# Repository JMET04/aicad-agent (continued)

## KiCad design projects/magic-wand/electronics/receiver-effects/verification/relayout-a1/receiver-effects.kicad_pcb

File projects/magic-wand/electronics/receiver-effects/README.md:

# Receiver Effects A0

Status: design input only; fabrication is blocked.

This is the independent media receiver direction. It is intentionally separate
from both the existing receiver baseline and the wand order. It contains only
the NINA-B302 radio/MCU concept, protected 5 V / 2 A USB-C input, 3.3 V logic,
an 8-pin GC9A01A module interface, MAX98357A I2S amplifier with differential
4 ohm speaker connector, and a discrete 3.3 V RGB status LED. Legacy UART,
optocoupler and 12 V MOSFET actuator channels are not copied.

The exact pin, power, effect and resource design inputs are in
receiver-effects-contract.json. fabrication-gate.json is authoritative for
ordering: there are no KiCad sources, native ERC/DRC, Gerber, drill, qualified
BOM or placement files yet, so fabrication_authorized is false.

The portable firmware can host-test eight isolated sessions and procedural
display/audio effects. That evidence does not close target, power, RF, EMC,
thermal, acoustic or manufacturing gates.

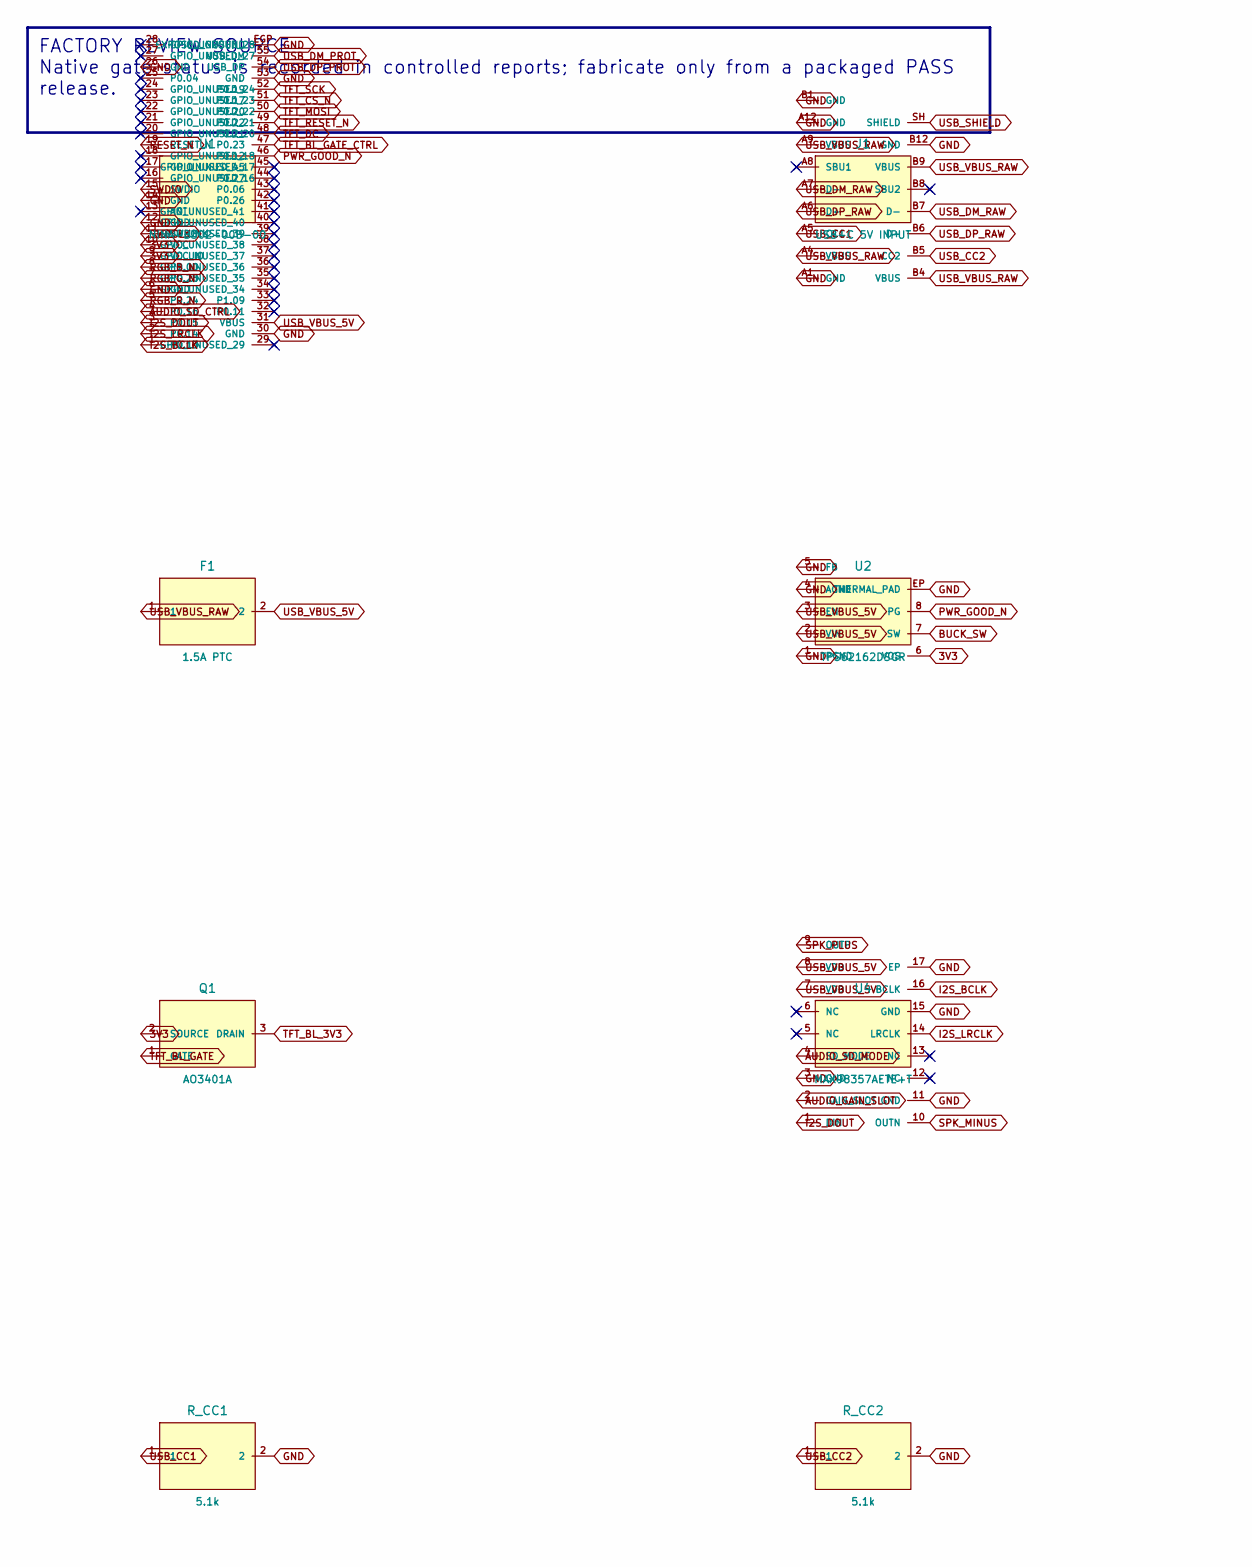
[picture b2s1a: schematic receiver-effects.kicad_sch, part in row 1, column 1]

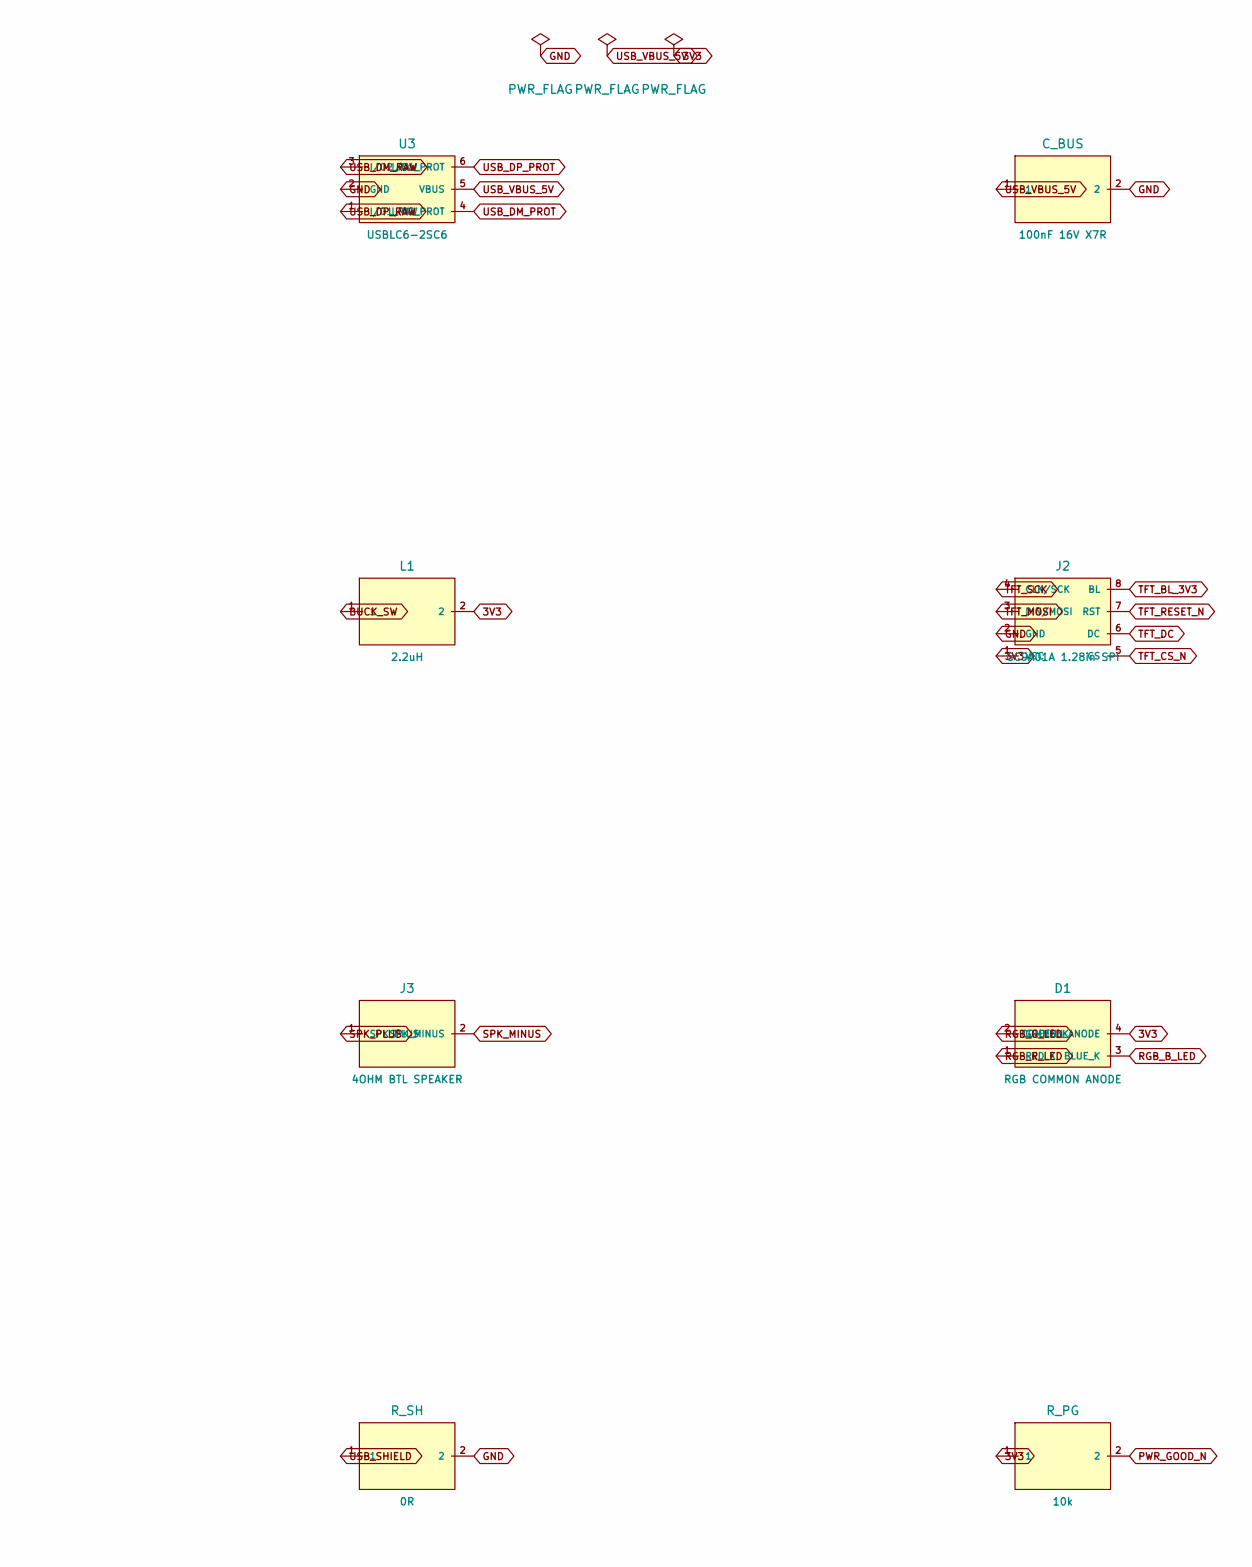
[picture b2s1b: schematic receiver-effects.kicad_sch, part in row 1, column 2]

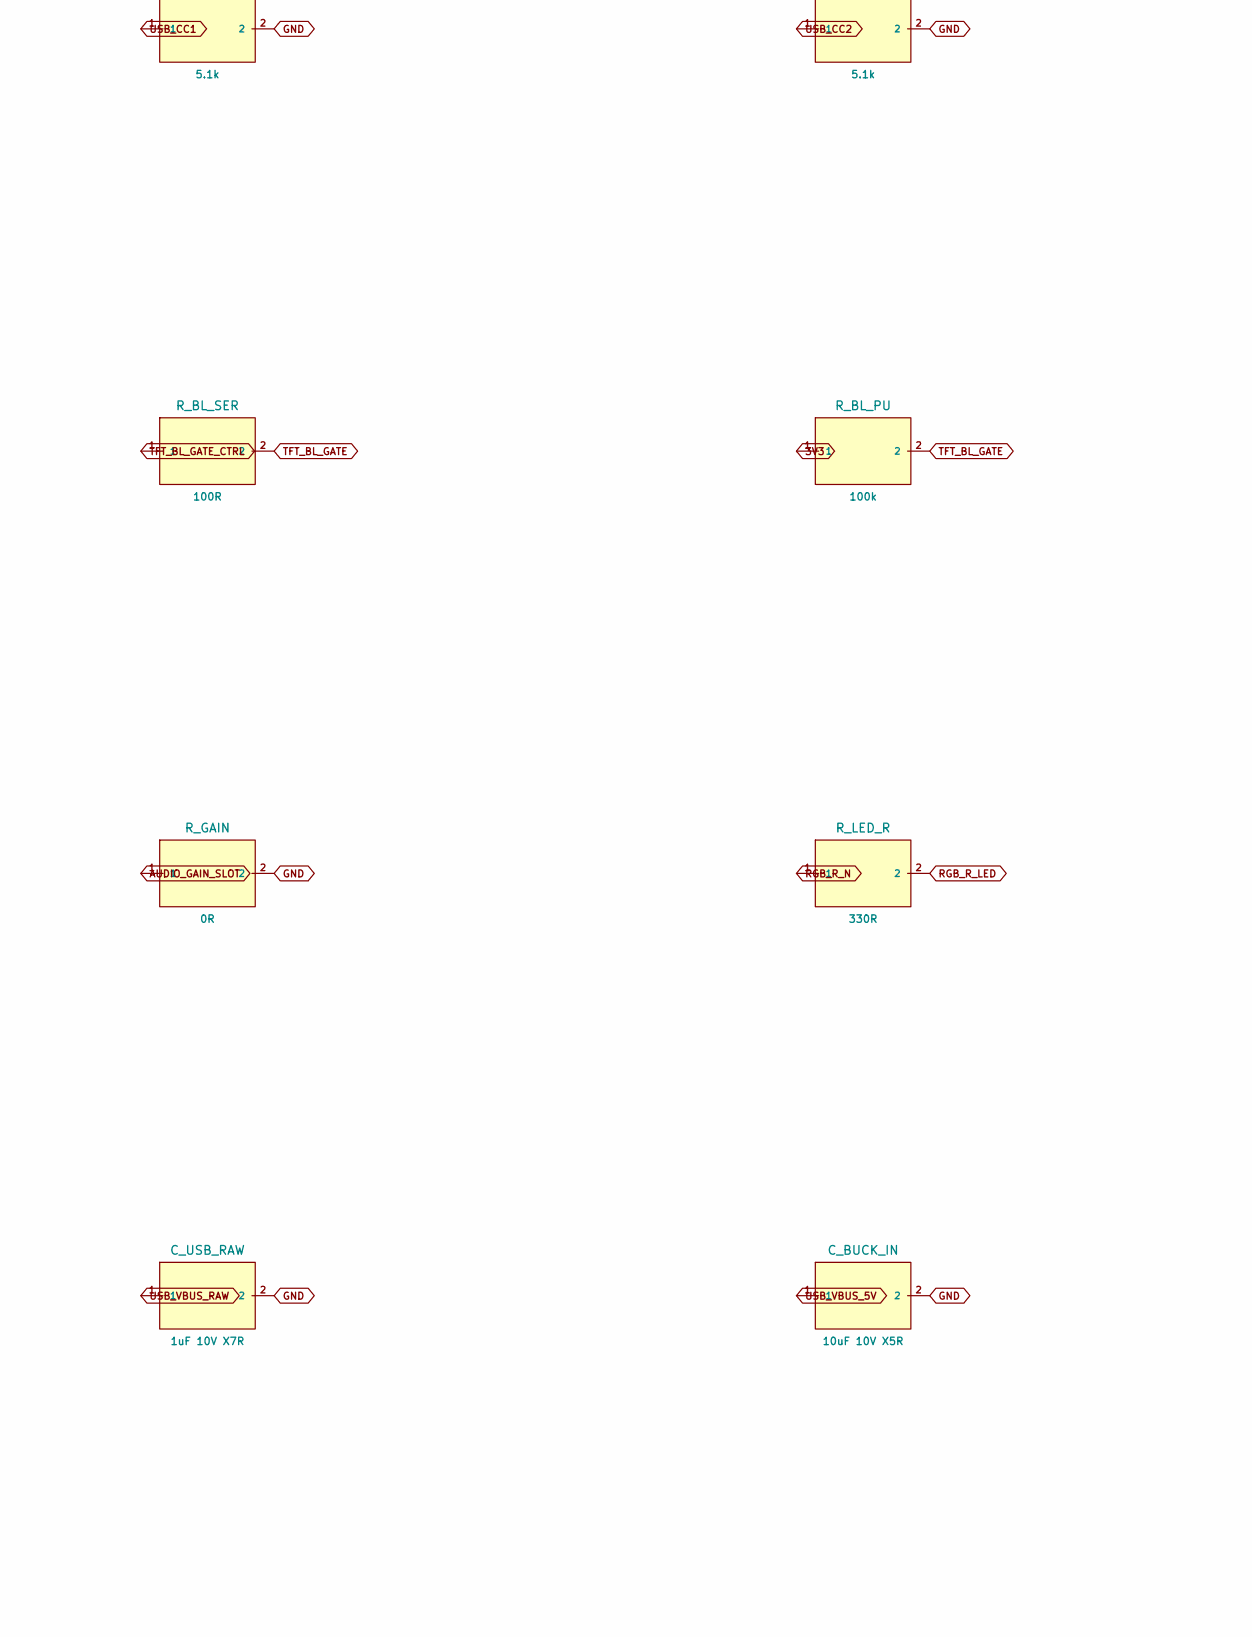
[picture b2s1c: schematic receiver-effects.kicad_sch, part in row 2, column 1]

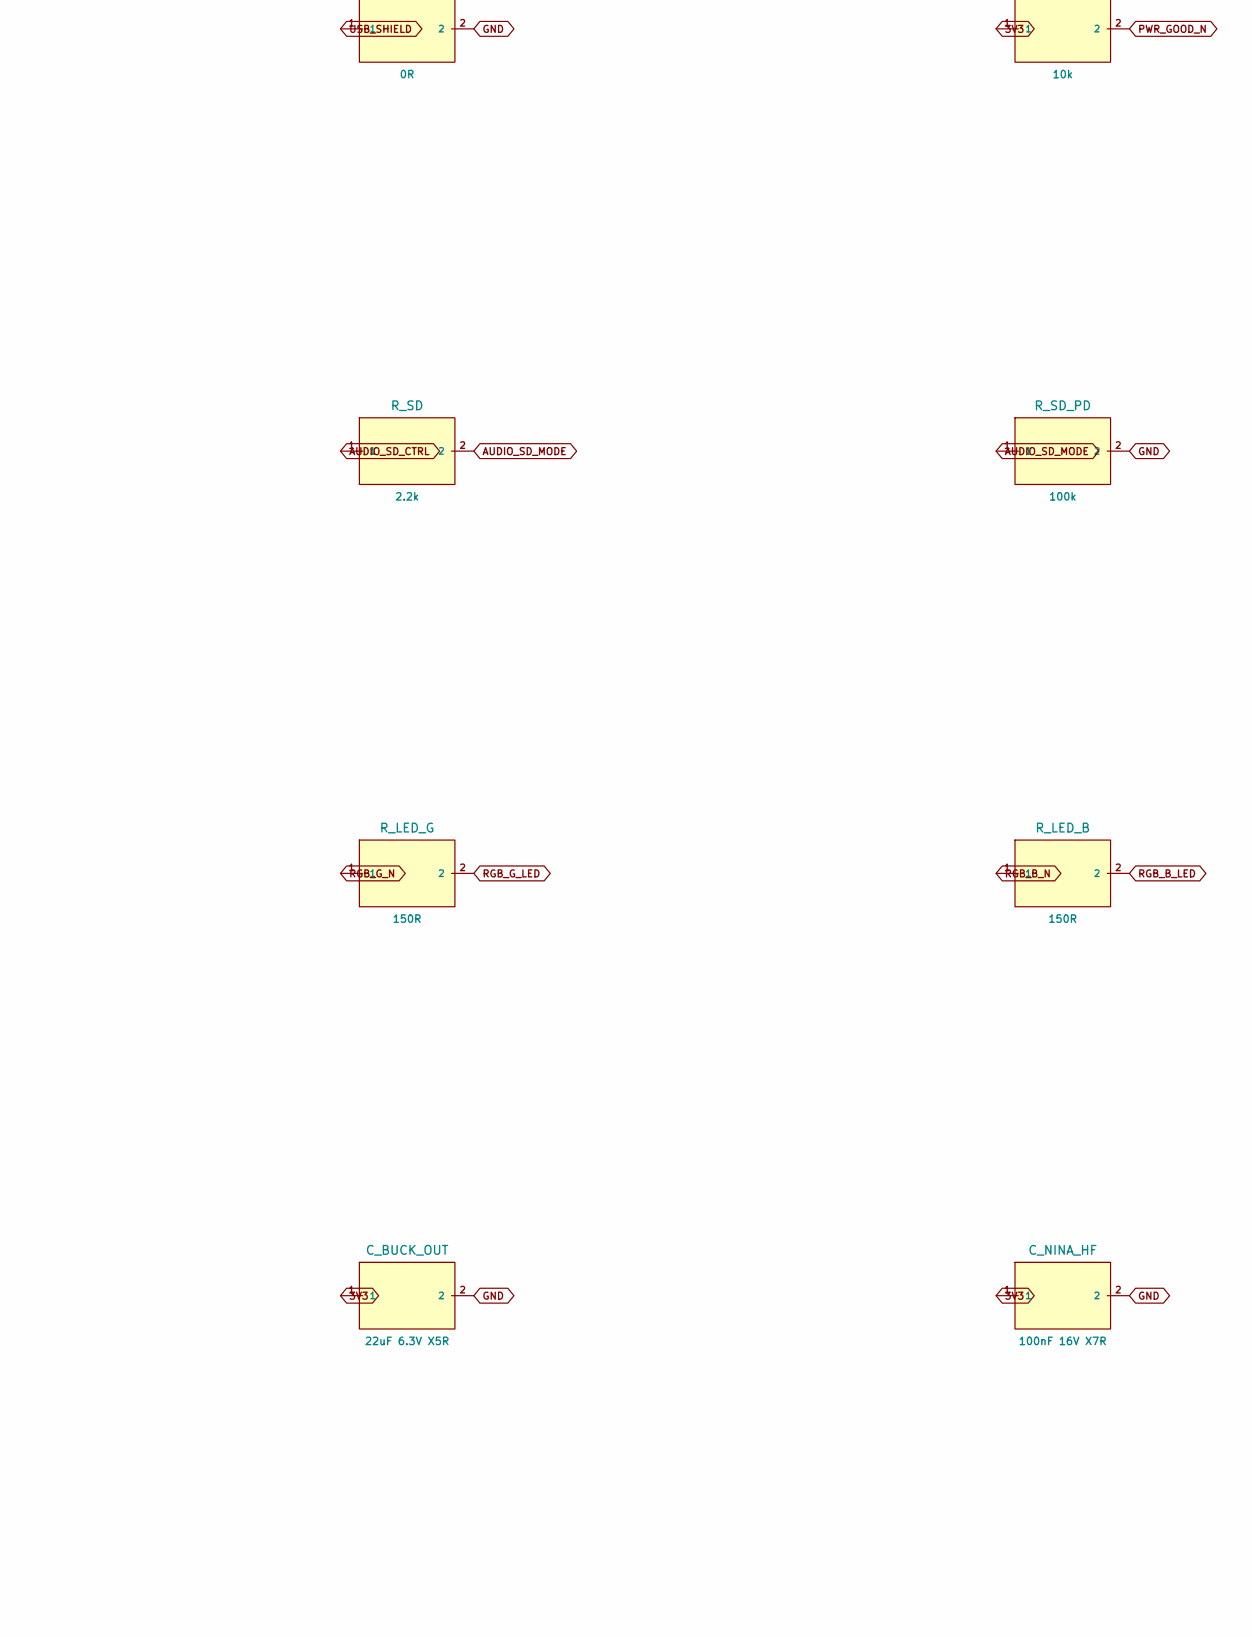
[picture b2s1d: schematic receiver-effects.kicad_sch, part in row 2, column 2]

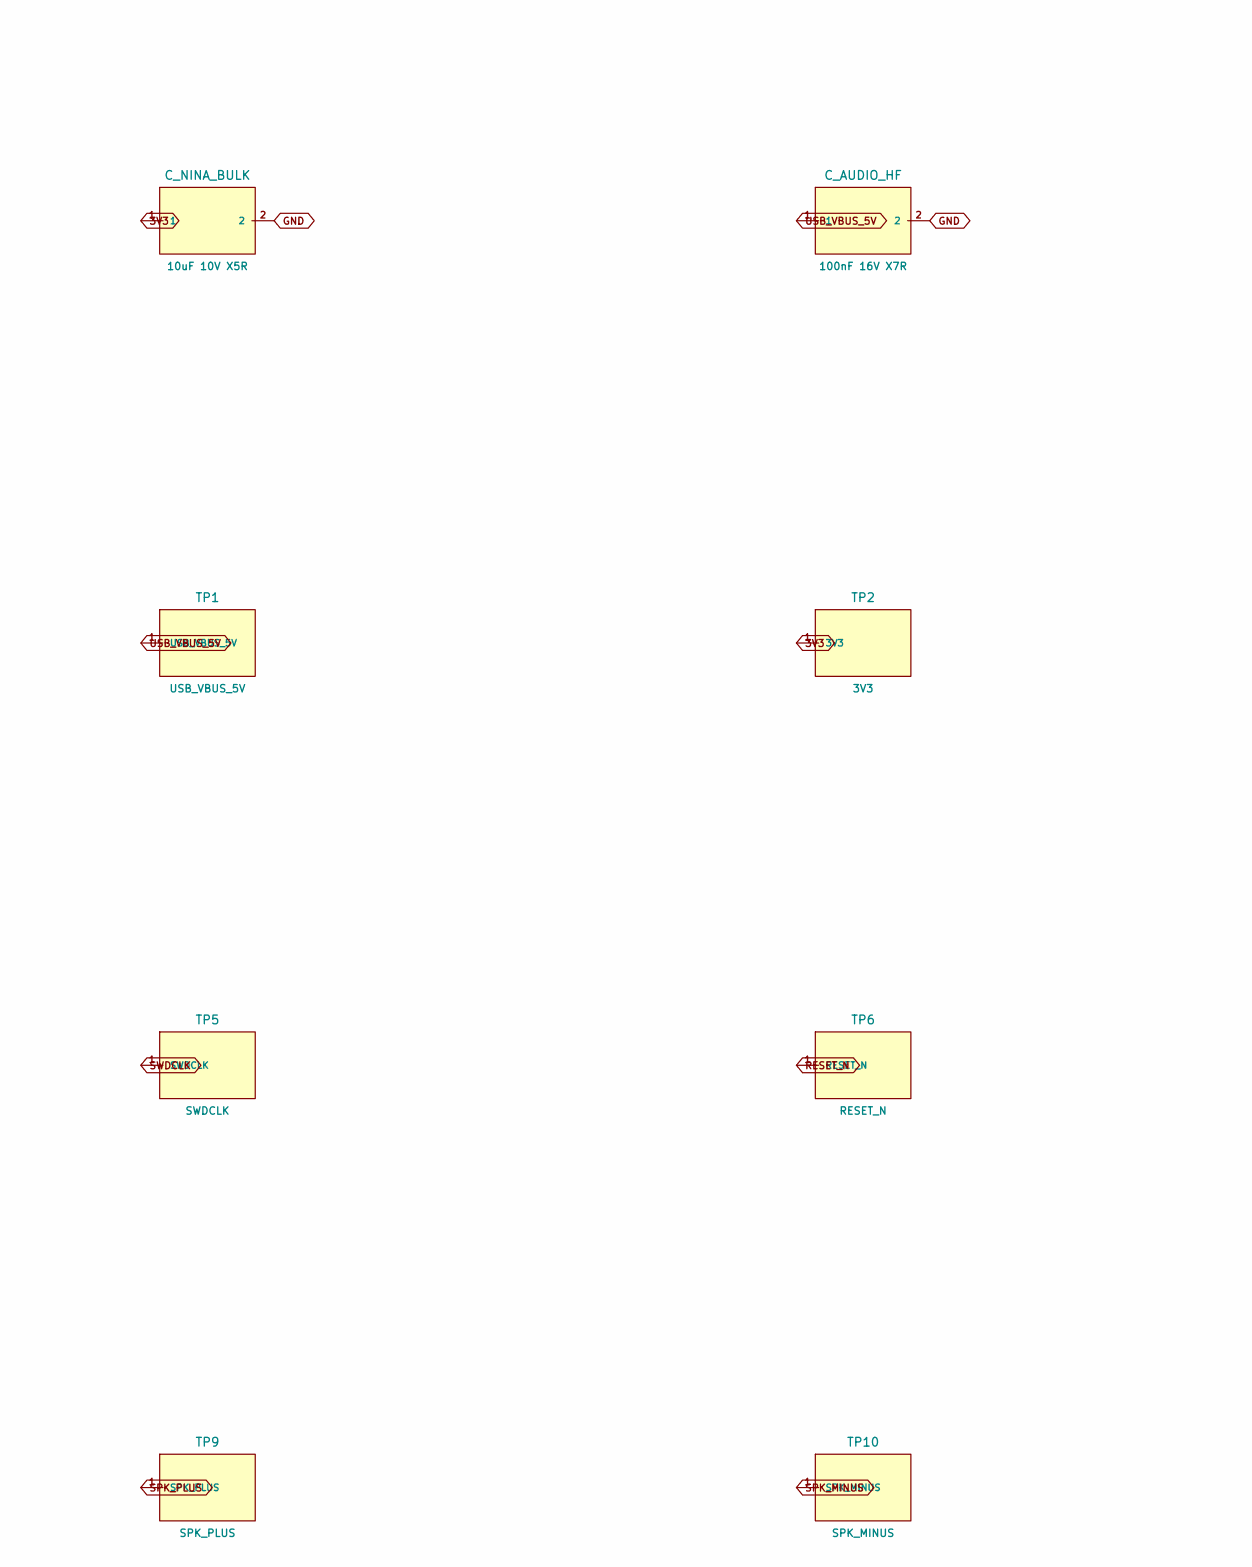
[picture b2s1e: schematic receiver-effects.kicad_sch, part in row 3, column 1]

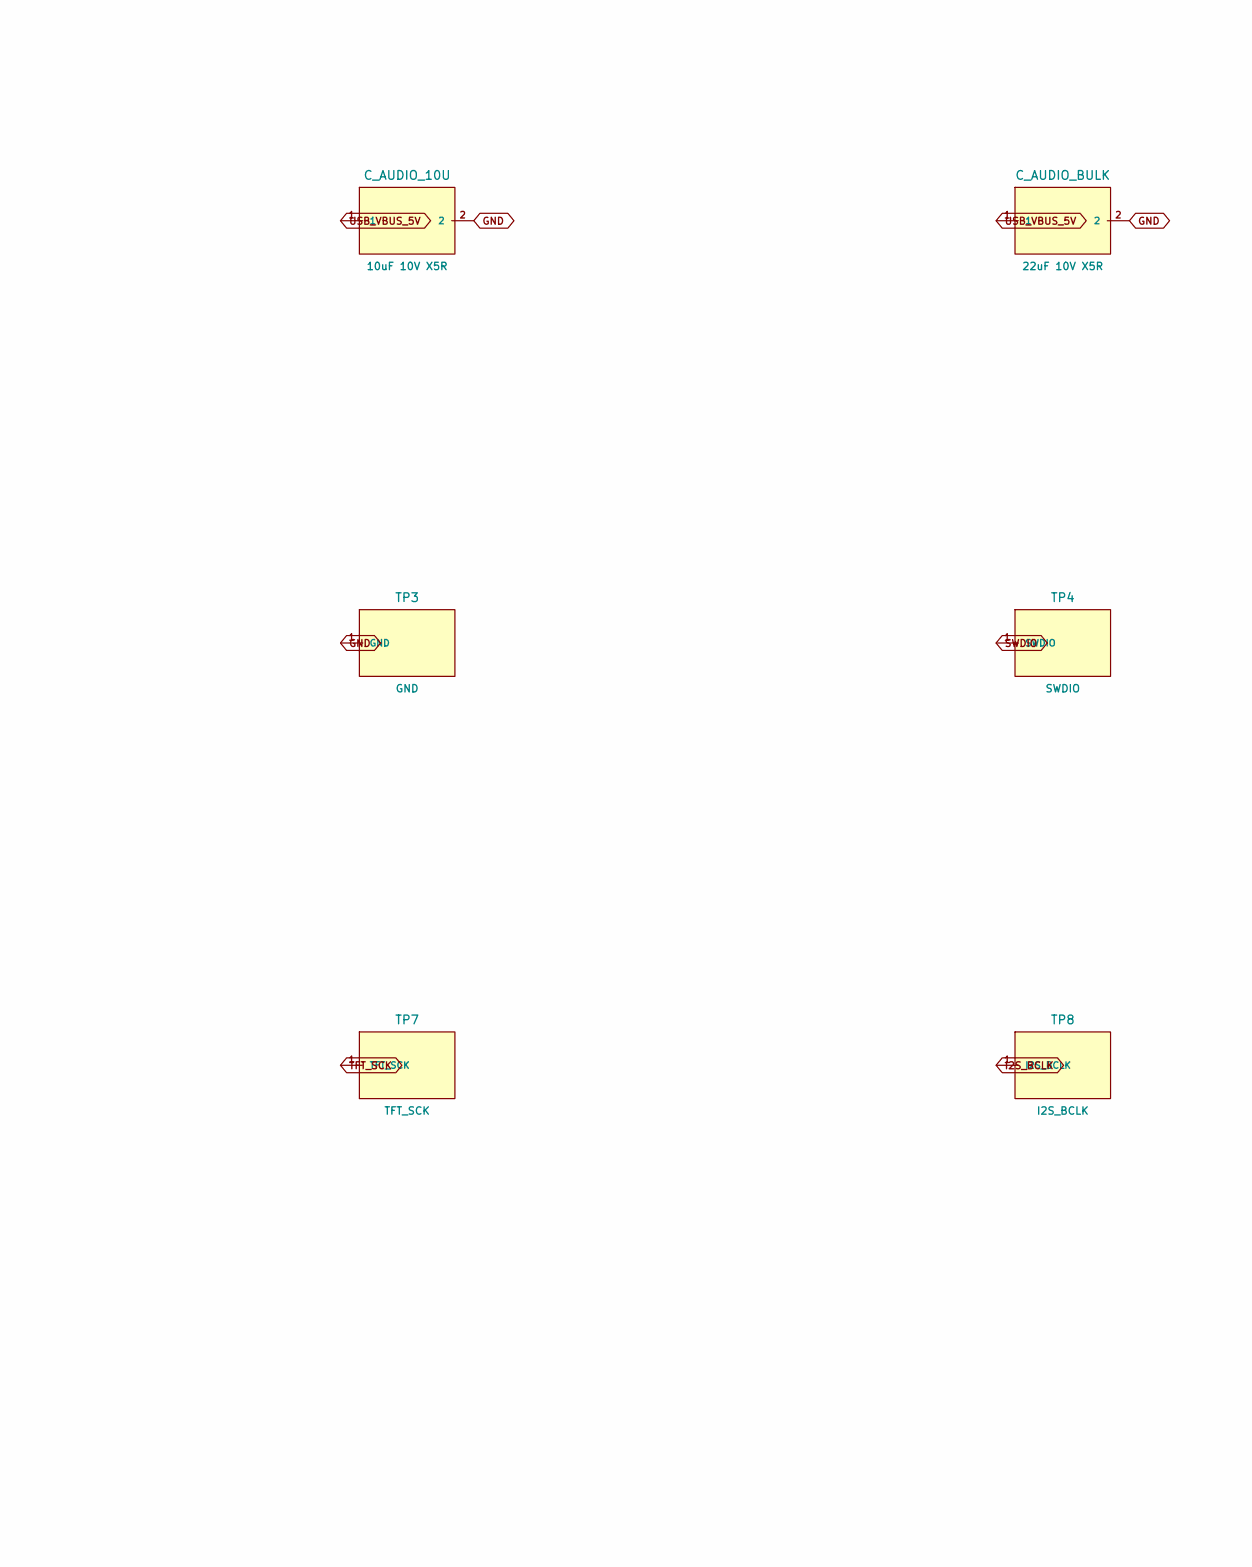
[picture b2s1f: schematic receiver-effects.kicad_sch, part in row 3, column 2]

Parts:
C_AUDIO_10U: 10uF 10V X5R; receiver-effects_C_AUDIO_10U; MPN GRM21BR61A106KE19L; LCSC C77073
C_AUDIO_BULK: 22uF 10V X5R; receiver-effects_C_AUDIO_BULK; MPN GRM21BR61A226ME44L; LCSC C441864
C_AUDIO_HF: 100nF 16V X7R; receiver-effects_C_AUDIO_HF; MPN GRM155R71C104KA88D; LCSC C1525
C_BUCK_IN: 10uF 10V X5R; receiver-effects_C_BUCK_IN; MPN GRM21BR61A106KE19L; LCSC C77073
C_BUCK_OUT: 22uF 6.3V X5R; receiver-effects_C_BUCK_OUT; MPN GRM21BR60J226ME39L; LCSC C77071
C_BUS: 100nF 16V X7R; receiver-effects_C_BUS; MPN GRM155R71C104KA88D; LCSC C1525
C_NINA_BULK: 10uF 10V X5R; receiver-effects_C_NINA_BULK; MPN GRM21BR61A106KE19L; LCSC C77073
C_NINA_HF: 100nF 16V X7R; receiver-effects_C_NINA_HF; MPN GRM155R71C104KA88D; LCSC C1525
C_USB_RAW: 1uF 10V X7R; receiver-effects_C_USB_RAW; MPN GRM155R71A105KE15D
D1: RGB COMMON ANODE; receiver-effects_D1; MPN LTST-C19HE1WT; LCSC C458749
F1: 1.5A PTC; receiver-effects_F1; MPN MF-MSMF150/24X-2; LCSC C78695
J1: USB-C 5V INPUT; receiver-effects_J1; MPN USB4105-GF-A-120; LCSC C5184243
J2: GC9A01A 1.28in SPI; receiver-effects_J2; MPN SM08B-GHS-TB(LF)(SN); LCSC C265111
J3: 4OHM BTL SPEAKER; receiver-effects_J3; MPN S2B-PH-SM4-TB(LF)(SN); LCSC C295747
L1: 2.2uH; receiver-effects_L1; MPN LQH32PN2R2NN0L
Q1: AO3401A; receiver-effects_Q1; MPN AO3401A; LCSC C15127
R_BL_PU: 100k; receiver-effects_R_BL_PU; MPN RC0402FR-07100KL; LCSC C25741
R_BL_SER: 100R; receiver-effects_R_BL_SER; MPN RC0402FR-07100RL; LCSC C25076
R_CC1: 5.1k; receiver-effects_R_CC1; MPN RC0402FR-075K1L; LCSC C25905
R_CC2: 5.1k; receiver-effects_R_CC2; MPN RC0402FR-075K1L; LCSC C25905
R_GAIN: 0R; receiver-effects_R_GAIN; MPN RC0402JR-070RL; LCSC C17168
R_LED_B: 150R; receiver-effects_R_LED_B; MPN RC0402FR-07150RL; LCSC C25082
R_LED_G: 150R; receiver-effects_R_LED_G; MPN RC0402FR-07150RL; LCSC C25082
R_LED_R: 330R; receiver-effects_R_LED_R; MPN RC0402FR-07330RL; LCSC C25104
R_PG: 10k; receiver-effects_R_PG; MPN RC0402FR-0710KL; LCSC C25744
R_SD: 2.2k; receiver-effects_R_SD; MPN RC0402FR-072K2L; LCSC C25879
R_SD_PD: 100k; receiver-effects_R_SD_PD; MPN RC0402FR-07100KL; LCSC C25741
R_SH: 0R; receiver-effects_R_SH; MPN RC0402JR-070RL; LCSC C17168
TP1: USB_VBUS_5V; receiver-effects_TP1; MPN BARE_PAD_D1.5
TP2: 3V3; receiver-effects_TP2; MPN BARE_PAD_D1.5
TP3: GND; receiver-effects_TP3; MPN BARE_PAD_D1.5
TP4: SWDIO; receiver-effects_TP4; MPN BARE_PAD_D1.5
TP5: SWDCLK; receiver-effects_TP5; MPN BARE_PAD_D1.5
TP6: RESET_N; receiver-effects_TP6; MPN BARE_PAD_D1.5
TP7: TFT_SCK; receiver-effects_TP7; MPN BARE_PAD_D1.5
TP8: I2S_BCLK; receiver-effects_TP8; MPN BARE_PAD_D1.5
TP9: SPK_PLUS; receiver-effects_TP9; MPN BARE_PAD_D1.5
TP10: SPK_MINUS; receiver-effects_TP10; MPN BARE_PAD_D1.5
U1: NINA-B302-00B-00; receiver-effects_U1; MPN NINA-B302-00B-00; LCSC C6335962
U2: TPS62162DSGR; receiver-effects_U2; MPN TPS62162DSGR; LCSC C40256
U3: USBLC6-2SC6; receiver-effects_U3; MPN USBLC6-2SC6; LCSC C7519
U4: MAX98357AETE+T; receiver-effects_U4; MPN MAX98357AETE+T; LCSC C910544

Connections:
3V3: C_BUCK_OUT.1, C_NINA_BULK.1, C_NINA_HF.1, D1.4 (COMMON_ANODE), J2.1 (VCC), L1.2, Q1.2 (SOURCE), R_BL_PU.1, R_PG.1, TP2.1 (3V3), U1.9 (VCC_IO), U1.10 (VCC), U2.6 (VOS)
AUDIO_GAIN_SLOT: R_GAIN.1, U4.2 (GAIN_SLOT)
AUDIO_SD_CTRL: R_SD.1, U1.4 (P0.16)
AUDIO_SD_MODE: R_SD.2, R_SD_PD.1, U4.4 (SD_MODE)
BUCK_SW: L1.1, U2.7 (SW)
GND: C_AUDIO_10U.2, C_AUDIO_BULK.2, C_AUDIO_HF.2, C_BUCK_IN.2, C_BUCK_OUT.2, C_BUS.2, C_NINA_BULK.2, C_NINA_HF.2, C_USB_RAW.2, J1.A1 (GND), J1.A12 (GND), J1.B1 (GND), J1.B12 (GND), J2.2 (GND), R_CC1.2, R_CC2.2, R_GAIN.2, R_SD_PD.2, R_SH.2, TP3.1 (GND), U1.6 (GND), U1.12 (GND), U1.14 (GND), U1.26 (GND), U1.30 (GND), U1.53 (GND), U1.EGP (EXPOSED_GROUND), U2.1 (PGND), U2.4 (AGND), U2.5 (FB), U2.EP (THERMAL_PAD), U3.2 (GND), U4.3 (GND), U4.11 (GND), U4.15 (GND), U4.17 (EP)
I2S_BCLK: TP8.1 (I2S_BCLK), U1.1 (P0.13), U4.16 (BCLK)
I2S_DOUT: U1.3 (P0.15), U4.1 (DIN)
I2S_LRCLK: U1.2 (P0.14), U4.14 (LRCLK)
PWR_GOOD_N: R_PG.2, U1.46 (P0.12), U2.8 (PG)
RESET_N: TP6.1 (RESET_N), U1.19 (RESET_N)
RGB_B_LED: D1.3 (BLUE_K), R_LED_B.2
RGB_B_N: R_LED_B.1, U1.8 (P1.00)
RGB_G_LED: D1.2 (GREEN_K), R_LED_G.2
RGB_G_N: R_LED_G.1, U1.7 (P0.25)
RGB_R_LED: D1.1 (RED_K), R_LED_R.2
RGB_R_N: R_LED_R.1, U1.5 (P0.24)
SPK_MINUS: J3.2 (SPK_MINUS), TP10.1 (SPK_MINUS), U4.10 (OUTN)
SPK_PLUS: J3.1 (SPK_PLUS), TP9.1 (SPK_PLUS), U4.9 (OUTP)
SWDCLK: TP5.1 (SWDCLK), U1.11 (SWDCLK)
SWDIO: TP4.1 (SWDIO), U1.15 (SWDIO)
TFT_BL_3V3: J2.8 (BL), Q1.3 (DRAIN)
TFT_BL_GATE: Q1.1 (GATE), R_BL_PU.2, R_BL_SER.2
TFT_BL_GATE_CTRL: R_BL_SER.1, U1.47 (P0.23)
TFT_CS_N: J2.5 (CS), U1.51 (P0.17)
TFT_DC: J2.6 (DC), U1.48 (P0.21)
TFT_MOSI: J2.3 (DIN/MOSI), U1.50 (P0.20)
TFT_RESET_N: J2.7 (RST), U1.49 (P0.22)
TFT_SCK: J2.4 (CLK/SCK), TP7.1 (TFT_SCK), U1.52 (P0.19)
USB_CC1: J1.A5 (CC1), R_CC1.1
USB_CC2: J1.B5 (CC2), R_CC2.1
USB_DM_PROT: U1.55 (USB_DM), U3.4 (I/O2_PROT)
USB_DM_RAW: J1.A7 (D-), J1.B7 (D-), U3.3 (I/O2_RAW)
USB_DP_PROT: U1.54 (USB_DP), U3.6 (I/O1_PROT)
USB_DP_RAW: J1.A6 (D+), J1.B6 (D+), U3.1 (I/O1_RAW)
USB_SHIELD: J1.SH (SHIELD), R_SH.1
USB_VBUS_5V: C_AUDIO_10U.1, C_AUDIO_BULK.1, C_AUDIO_HF.1, C_BUCK_IN.1, C_BUS.1, F1.2, TP1.1 (USB_VBUS_5V), U1.31 (VBUS), U2.2 (VIN), U2.3 (EN), U3.5 (VBUS), U4.7 (VDD), U4.8 (VDD)
USB_VBUS_RAW: C_USB_RAW.1, F1.1, J1.A4 (VBUS), J1.A9 (VBUS), J1.B4 (VBUS), J1.B9 (VBUS)

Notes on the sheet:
FACTORY REVIEW SOURCE Native gate status is recorded in controlled reports; fabricate only from a packaged PASS release.

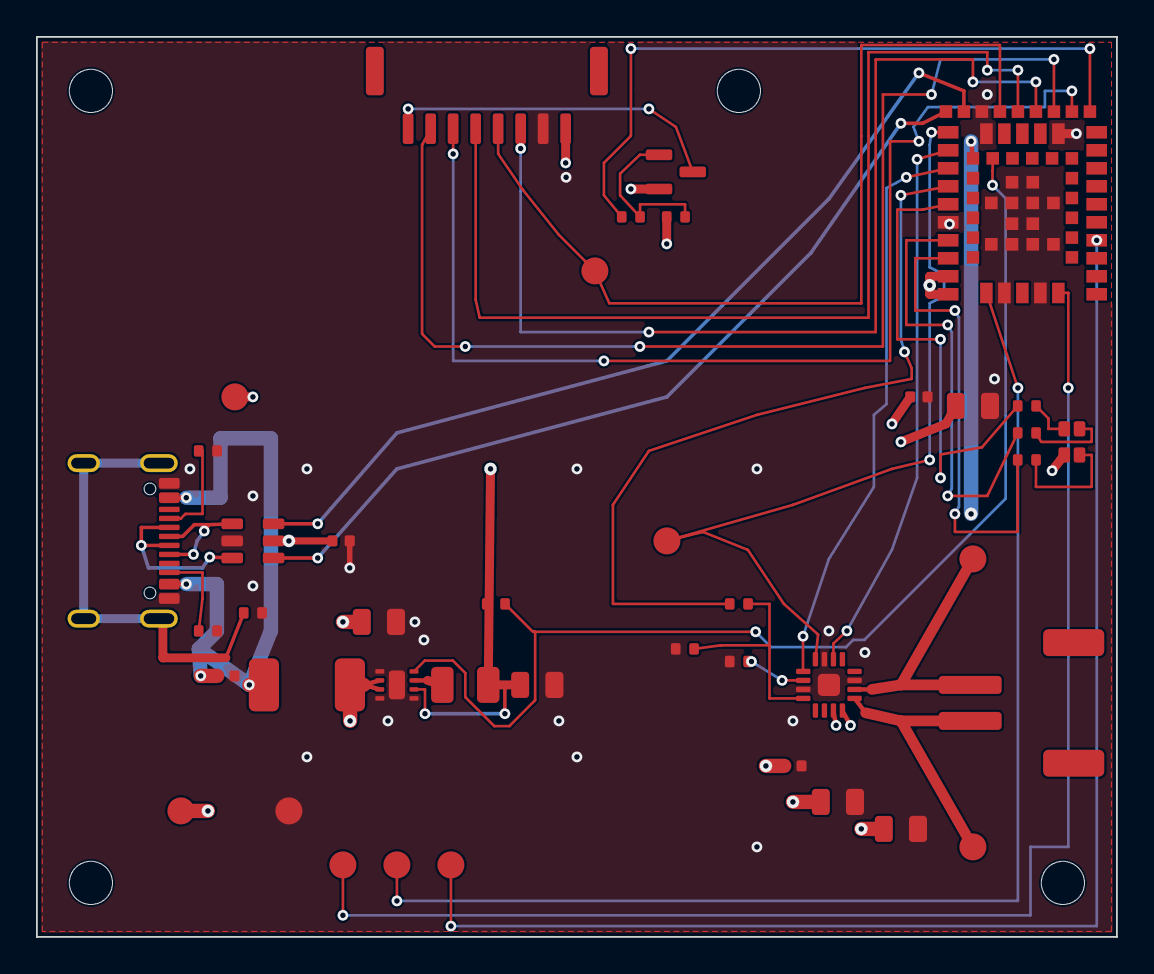
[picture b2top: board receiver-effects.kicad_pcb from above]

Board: 4 copper layers, 60.0 x 50.0 mm, 46 parts (0 on the bottom side), 38 nets.

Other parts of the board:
H1: MountingHole_2.4mm; receiver-effects_H1
H2: MountingHole_2.4mm; receiver-effects_H2
H3: MountingHole_2.4mm; receiver-effects_H3
H4: MountingHole_2.4mm; receiver-effects_H4
